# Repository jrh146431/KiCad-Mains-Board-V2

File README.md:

# KiCad-Mains-Board-V2
KiCad Mains Board V2

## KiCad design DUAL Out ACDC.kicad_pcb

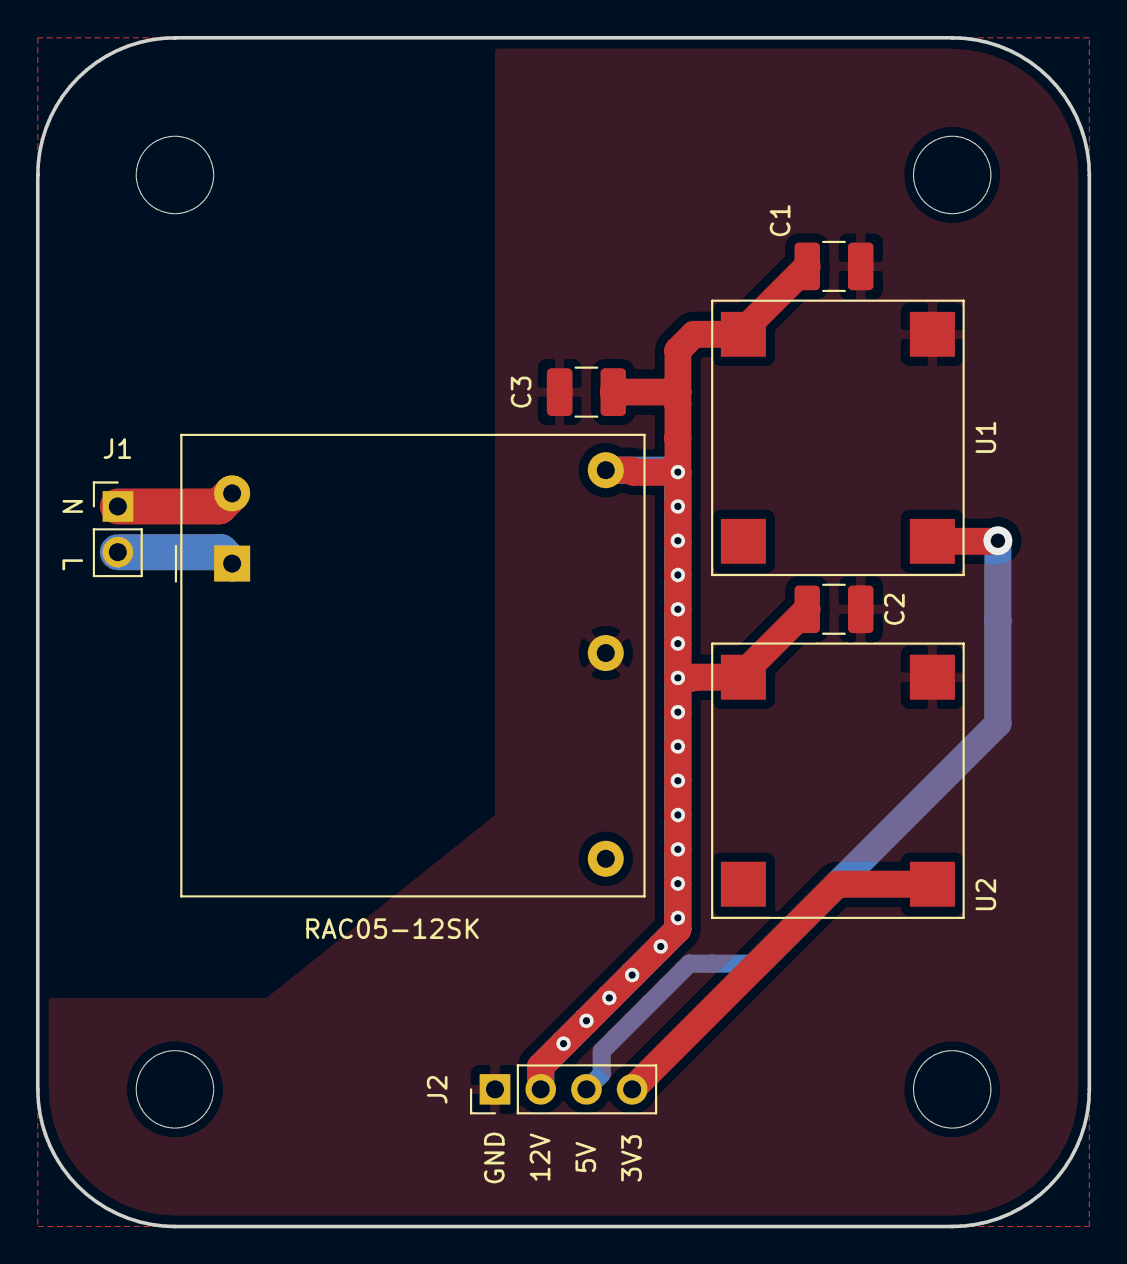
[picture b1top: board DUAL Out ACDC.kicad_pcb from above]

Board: 2 copper layers, 58.4 x 66.0 mm, 8 parts (0 on the bottom side), 6 nets.

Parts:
C1, C2, C3: 10uF; C_1210_3225Metric_Pad1.42x2.65mm_HandSolder
J1: Conn_01x02; PinHeader_1x02_P2.54mm_Vertical
J2: GND; PinHeader_1x04_P2.54mm_Vertical
RAC05-12SK: RAC05-12SK; Converter_ACDC_RECOM_RAC05-xxSK_THT
U1: ROF-78E5.0-0.5; ROF-78E
U2: ROF-78E3.3-0.5; ROF-78E

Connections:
+3V3: J2.4, U2.3
+5V: J2.3, U1.3
+12V: C1.1, C2.1, C3.1, J2.2, RAC05-12SK.5, U1.1, U2.1
GND: C1.2, C2.2, C3.2, J2.1, RAC05-12SK.4, U1.2, U2.2
L: J1.2, RAC05-12SK.1
N: J1.1, RAC05-12SK.2

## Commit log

2019-06-07 Create rea
